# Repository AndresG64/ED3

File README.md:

# Proyecto estación de soldadura.
Estación de soldadura con funcionalidades como establecer punto de temperatura y automatizaciones de seguridad.

## Funcionalidades:

- **Mango Cautín:** Aprovechando la casi linealidad entre el voltaje y temperatura del cautín es posible establecer una temperatura adecuada por medio de un PWM. (El Hakko 936 tiene un una resistencia interna o termopar K, que cambia según la temperatura).
- **Pantalla LCD:** Visualización en la pantalla del set point y temperatura actual.
- **Acelerómetro:** Detección de uso o actividad para desactivar el cautín de manera automática, establecer un modo reposo y bajar el consumo. Para calcular un golpe, active una alarma y desactive el sistema.
	
## Materiales:
- *Raspberry pi pico*
- *Fuente 24V 3A:* Alimentación del cautín.
- *Fuente 3.3V:* Para controlar la parte de control.
- *Hakko 936 50W*
- *Soporte para Cautín*
- *Pantalla LCD*
- *Módulo Acelerómetro ADXL335 análogo:* Control ADC de la raspberry pi pico.
- *Caja*
- *Mosfet de alta potencia:* Para el cautín.
- *Optocoplador:* Separamos la parte de control con la de potencia.
- *Leds:* Encendido o reposo.
- *Potenciometro:* Mediante el ADC regular la temperatura.

## Motivo
Pienso que es un proyecto que cumple con los requisitos y además útil para mi carrera, donde los materiales y conocimiento se seguirán usando en la carrera. También implementando métodos de seguridad y ahorro de energía puedo tener un cautín de alta gama por un precio reducido y hecho por mi.

# Informe Proyecto Final

## Resumen
Estación de soldadura basada en un control PID con lazo cerrado de retroalimentación. Se implementa la lectura por ADC para definir el setpoint y una salida PWM controlada por el PID para alcanzar la temperatura solicitada. Además, se mide continuamente el voltaje generado por la resistencia interna del cautín, el cual varía con la temperatura, con el fin de calcular el error actual y corregirlo en tiempo real.

## Procedimiento experimental y resultados

### Caracterización del Cautín
Para caracterizar la resistencia interna del cautín se implementó un programa utilizando el protocolo de comunicación SPI en conjunto con el módulo MAX6675, con el fin de capturar la temperatura medida por una termocupla. Esto permitió conectar el cautín directamente a 24 V y registrar tanto la variación de su resistencia como la temperatura de la punta, apoyándola sobre la termocupla. A partir de este procedimiento se obtuvo una tabla de Resistencia vs. Temperatura.

Posteriormente, empleando Excel fue posible calcular la relación entre temperatura y voltaje considerando una resistencia fija en serie de 1 kΩ y una alimentación de 3.3 V, correspondiente a la salida de la Raspberry Pi Pico. Sin embargo, la variación de voltaje dentro del rango de trabajo resultó muy pequeña, lo que reducía significativamente la resolución del ADC.

Para corregir esto, se optó por aprovechar completamente el rango del ADC mediante un amplificador operacional MOC6002 configurado en modo no inversor con una ganancia de 5. De esta manera, se amplificó la señal para obtener una mayor sensibilidad y una mejor resolución en la medición de temperatura.

### Etapa de potencia y control
Para garantizar un funcionamiento seguro y evitar fallos en el montaje, se consideró necesario separar la etapa de control de la etapa de potencia. Para ello se implementó un optoacoplador 4n26 que trabajará a una frecuencia de 1KHz, cuya salida opera a 5V mediante un convertidor reductor LM2596, elegido por su buena capacidad de disipación cuando se trabaja con 24 V de entrada.

La etapa de conmutación utiliza un transistor 2N2222 junto con un MOSFET IRF3708, el cual entra en conducción plena con un voltaje de compuerta cercano a 4.4 V y una resistencia serie de 110 Ω. Este arreglo permite controlar adecuadamente la corriente, habilitando o bloqueando el paso entre el drenaje y la fuente del MOSFET. Su uso también es conveniente debido a la salida invertida del optoacoplador, situación que se corrige empleando el transistor en configuración adecuada. Además, se incorporó una resistencia pull-down en la compuerta para asegurar que el MOSFET permanezca apagado cuando el transistor no está activo.

### Control PID
En la etapa de control se realiza la lectura, mediante el ADC, de un potenciómetro de 10 kΩ conectado a 3.3 V del microcontrolador. Este voltaje se convierte de forma lineal a una temperatura dentro del rango establecido. El valor obtenido se utiliza como referencia para calcular el error frente a la temperatura medida en el cautín y aplicar las acciones proporcional, integral y derivativa necesarias.

Las constantes del PID se determinaron experimentalmente. Se inició ajustando la ganancia proporcional con valores muy bajos para observar si el sistema respondía con lentitud o si lograba alcanzar el setpoint. La ganancia Kp seleccionada proporciona una respuesta rápida y mantiene la temperatura dentro de un margen cercano al 5% del valor deseado. Para reducir las oscilaciones se ajustó la ganancia integral, eligiendo un valor aún menor, lo que permitió alcanzar una tolerancia aproximada del 2%, adecuada para este tipo de control. La ganancia derivativa no fue necesaria debido a la buena estabilidad obtenida con las acciones proporcional e integral.

## Conclusiones
-   El análisis experimental del comportamiento de las ganancias del control PID es posible a partir del ensayo y visualización del comportamiento a través del monitor serial para corregir y establecer parámetros.

-   La carácterización de la tabla Resistencia vs Temperatura fue buena práctica para interpolar y tomar la decición de amplificar la salida con el fin de ganar mas resolución.

-   El uso del optocoplador 4n26 resultó trabajar bien a frecuencia de 1Khz aún teniendo una respuesta lenta y carácterizado al tener corrientes de fuja a frecuencias altas.

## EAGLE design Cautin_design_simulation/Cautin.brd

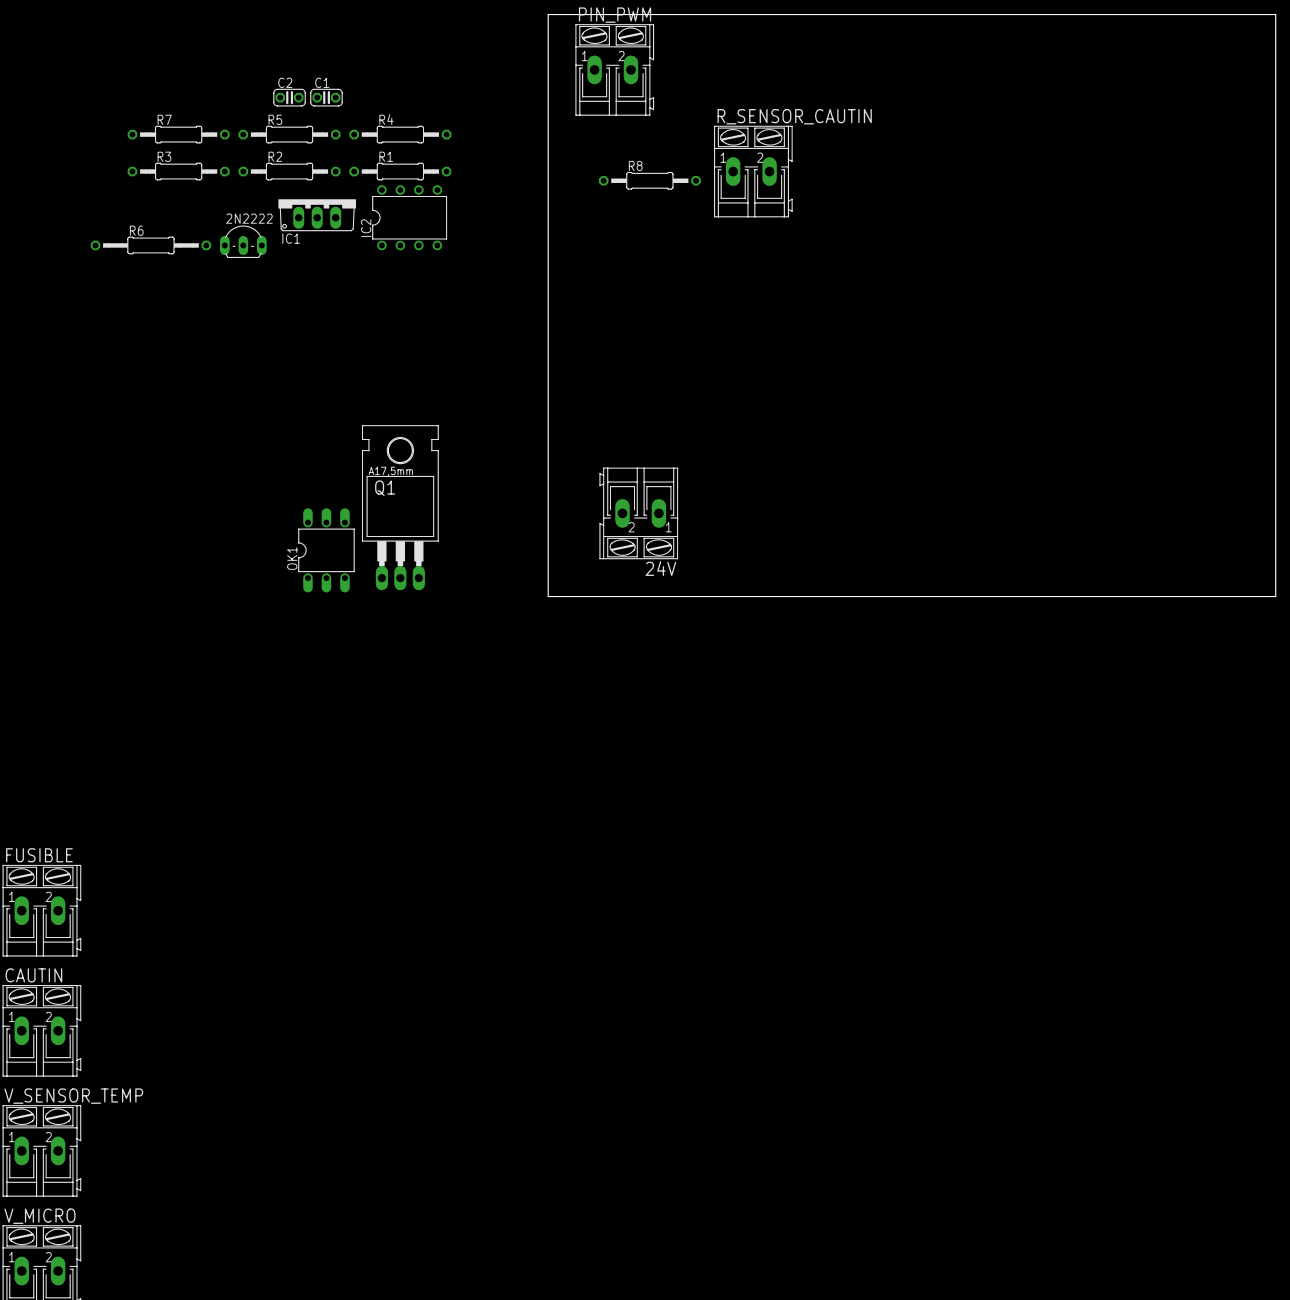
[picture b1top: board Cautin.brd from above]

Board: 2 copper layers, 100.0 x 80.0 mm, 22 parts (0 on the bottom side), 16 nets, no tracks yet.

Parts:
2N2222: TO92-EBC
24V: AK300/2
C1, C2: C025-024X044
CAUTIN: AK300/2
FUSIBLE: AK300/2
IC1: 7805TV; TO220V
IC2: LM358N; DIL08
OK1: 4N26M; DIL06
PIN_PWM: AK300/2
Q1: IRF3704; TO220AH
R1, R2, R3, R4, R5, R7, R8: 0207/12
R6: 0207/15
R_SENSOR_CAUTIN: AK300/2
V_MICRO: AK300/2
V_SENSOR_TEMP: AK300/2

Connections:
unnamed: OK1.1, PIN_PWM.1
unnamed: C2.1, IC1.1, R5.2
unnamed: 24V.1, FUSIBLE.1
unnamed: 24V.2, C1.2, C2.2, IC1.2, OK1.4, Q1.E, R1.2
unnamed: OK1.5, R3.1, R5.1
unnamed: 2N2222.B, R3.2
unnamed: 2N2222.E, R1.1, R2.1
unnamed: Q1.B, R2.2
unnamed: CAUTIN.2, Q1.C
unnamed: IC2.2, R4.1, R7.2
unnamed: IC2.3, R8.1, R_SENSOR_CAUTIN.1
unnamed: 2N2222.C, R6.1
unnamed: IC2.1, R4.2, V_SENSOR_TEMP.1
unnamed: C1.1, CAUTIN.1, FUSIBLE.2, IC1.3, R6.2
unnamed: OK1.2, PIN_PWM.2, R7.1, R_SENSOR_CAUTIN.2, V_MICRO.2, V_SENSOR_TEMP.2
unnamed: R8.2, V_MICRO.1

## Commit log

2025-10-24 delete
2025-10-24 Update soldering station project details
    Added potentiometer for temperature regulation via ADC.
2025-10-24 Add project motivation section to documentation
    Added a new section explaining the project's motivation and its relevance to my career.
2025-10-24 Initialize README with project details
    Added project description and features for soldering station.
2025-12-07 Simulación en proteus y diseño en eagle
2025-12-07 Simulación y diseño circuito
    Contiene la simulación en proteus y diseño en eagle de la parte de control y potencia.
2025-12-07 Primer commit
    La creación del folder que contiene el código para el micro
2025-12-07 Modulo ADC del potenciometro
2025-12-07 Modulo adc potenciometro
2025-12-07 Documentación Doxygen adc_setpoint.c
2025-12-08 commit PID
2025-12-10 Caracterización temperatura y resistencia Excel
2025-12-10 Actualización simulación proteus
2025-12-10 Commit proteus (Nombre de variable)
2025-12-10 Commit sensor de temperatura
2025-12-10 adc_temp commit
    Se desarrolla el módulo adc para la lectura e interpolación de los datos recibidos
2025-12-10 Modulo lcd commit
    Desarrollo de la librería lcd
2025-12-10 actualización CMake commit
2025-12-11 arreglos pequeños proteus commit
2025-12-11 Correcciones duty commit
2025-12-11 Actualización final commit
2025-12-11 commit simulacion
2025-12-11 Documentación Doxygen commit
2025-12-11 Informe README commit
2025-12-12 commit Simulación
